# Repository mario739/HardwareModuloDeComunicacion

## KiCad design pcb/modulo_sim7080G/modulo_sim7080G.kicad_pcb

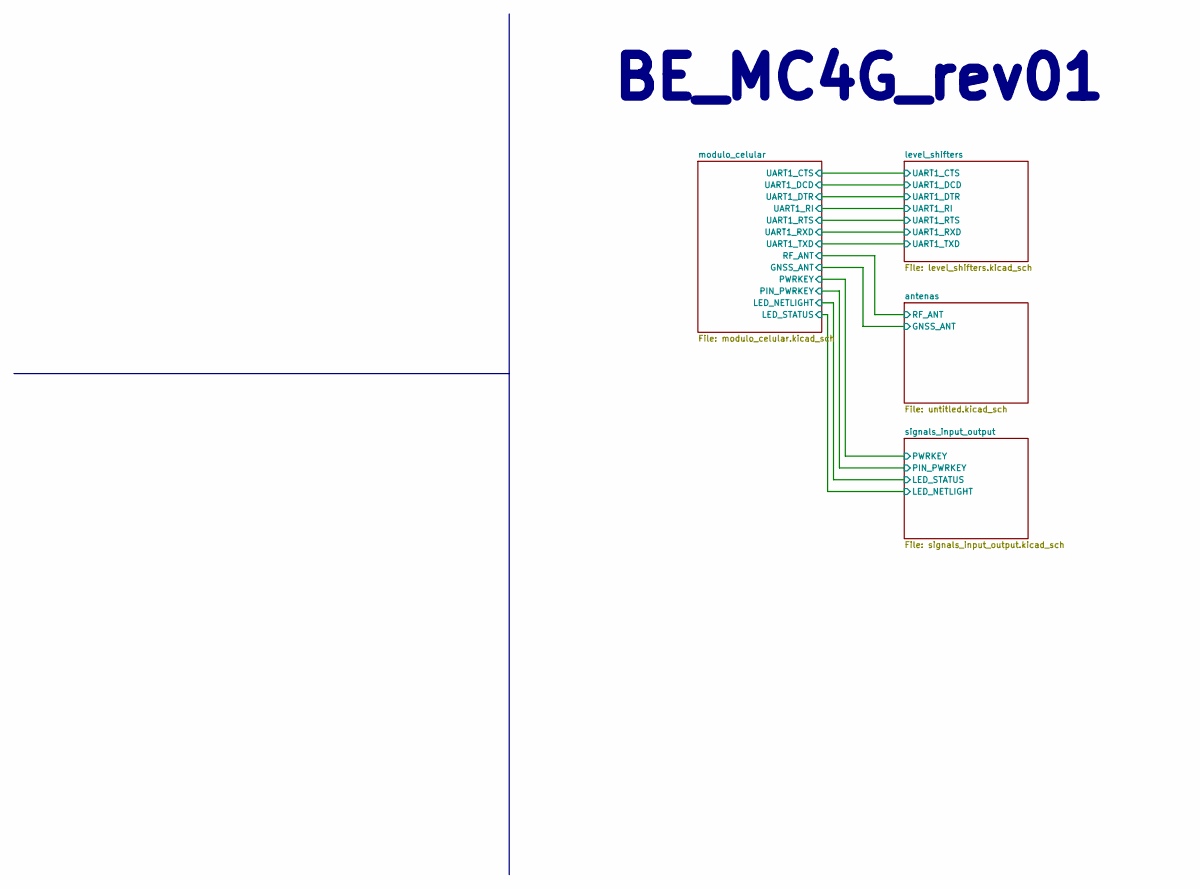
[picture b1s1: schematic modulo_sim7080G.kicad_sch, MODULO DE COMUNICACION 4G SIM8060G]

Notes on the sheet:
BE_MC4G_rev01

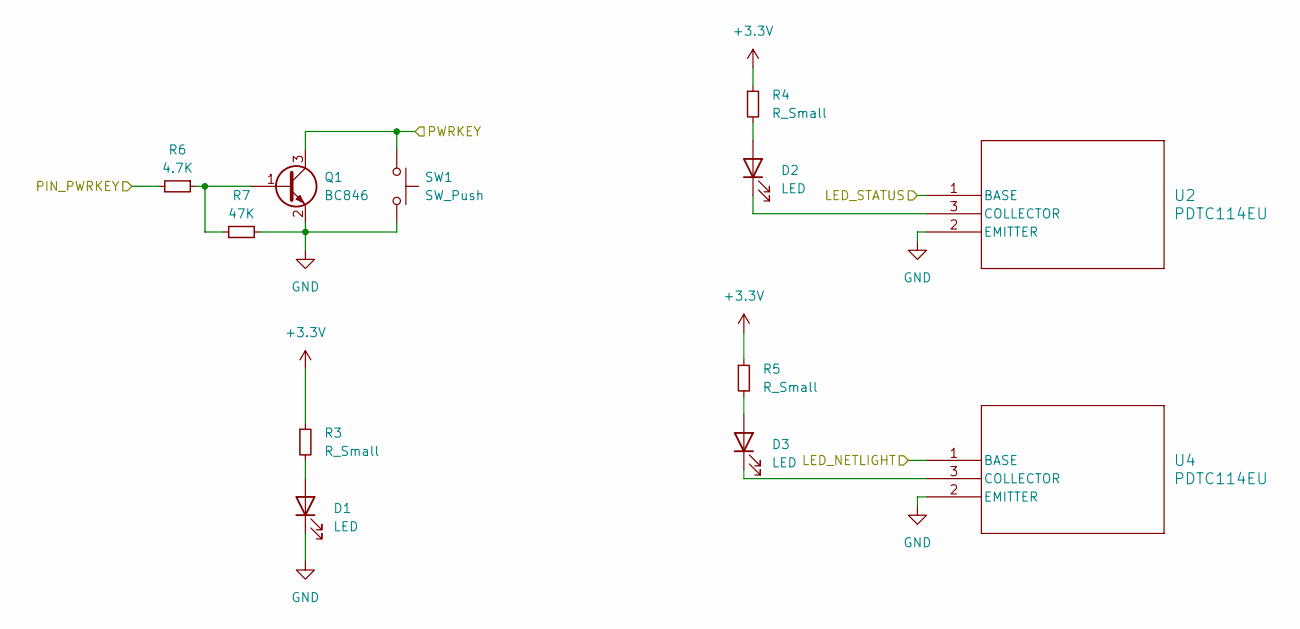
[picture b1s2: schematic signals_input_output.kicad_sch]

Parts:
D1, D2, D3: LED; LED_0805_2012Metric
Q1: BC846; SOT-23
R3, R4, R5: R_Small; R_0402_1005Metric
R6: 4.7K; R_0402_1005Metric
R7: 47K; R_0402_1005Metric
SW1: SW_Push; SW_SPST_B3U-1000P-B
U2, U4: PDTC114EU; SOT323_NEX

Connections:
+3.3V: R3.1, R4.1, R5.1; also elsewhere on the board
/modulo_celular/LED_NETLIGHT: U2.1 (BASE); also elsewhere on the board
/modulo_celular/LED_STATUS: U4.1 (BASE); also elsewhere on the board
/modulo_celular/PIN_PWRKEY: R6.2; also elsewhere on the board
/modulo_celular/PWRKEY: Q1.3 (C), SW1.1; also elsewhere on the board
GND: D1.1 (K), Q1.2 (E), R7.2, SW1.2, U2.2 (EMITTER), U4.2 (EMITTER); also elsewhere on the board
unnamed: D1.2 (A), R3.2
unnamed: D2.2 (A), R4.2
unnamed: D2.1 (K), U2.3 (COLLECTOR)
unnamed: D3.2 (A), R5.2
unnamed: D3.1 (K), U4.3 (COLLECTOR)
unnamed: Q1.1 (B), R6.1, R7.1

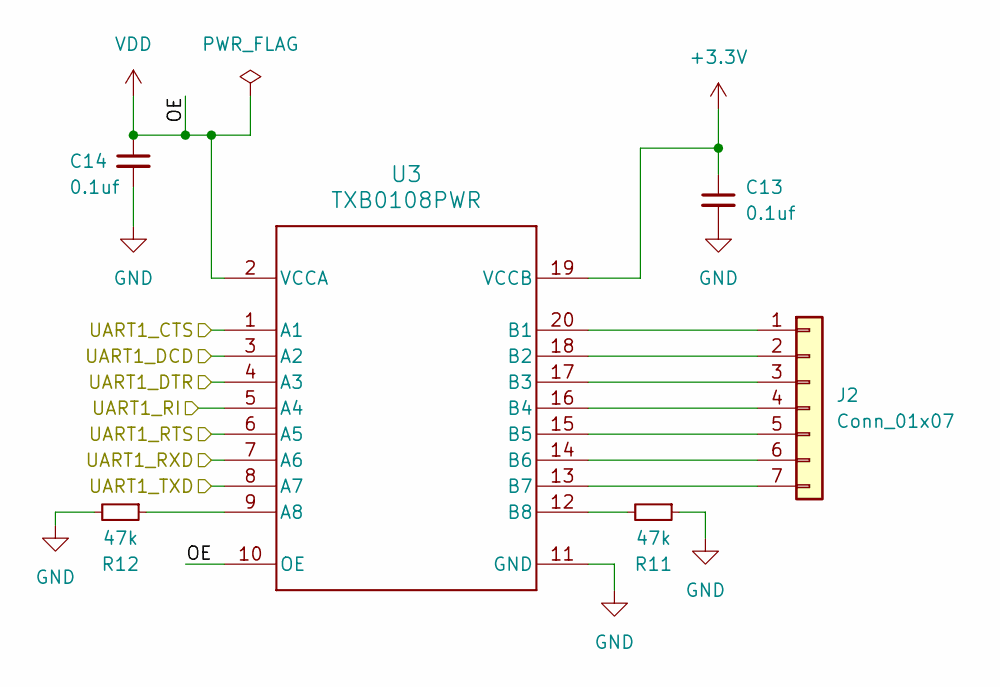
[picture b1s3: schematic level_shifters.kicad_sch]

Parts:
C13, C14: 0.1uf; C_0402_1005Metric
J2: Conn_01x07; PinHeader_1x07_P2.54mm_Vertical
R11, R12: 47k; R_0402_1005Metric
U3: TXB0108PWR; PW0020A_N

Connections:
+3.3V: C13.1, U3.19 (VCCB); also elsewhere on the board
/level_shifters/UART1_CTS: U3.1 (A1); also elsewhere on the board
/level_shifters/UART1_DCD: U3.3 (A2); also elsewhere on the board
/level_shifters/UART1_DTR: U3.4 (A3); also elsewhere on the board
/level_shifters/UART1_RI: U3.5 (A4); also elsewhere on the board
/level_shifters/UART1_RTS: U3.6 (A5); also elsewhere on the board
/level_shifters/UART1_RXD: U3.7 (A6); also elsewhere on the board
/level_shifters/UART1_TXD: U3.8 (A7); also elsewhere on the board
GND: C13.2, C14.2, R11.1, R12.2, U3.11 (GND); also elsewhere on the board
unnamed: J2.1, U3.20 (B1)
unnamed: J2.2, U3.18 (B2)
unnamed: J2.3, U3.17 (B3)
unnamed: J2.4, U3.16 (B4)
unnamed: J2.5, U3.15 (B5)
unnamed: J2.6, U3.14 (B6)
unnamed: J2.7, U3.13 (B7)
unnamed: R12.1, U3.9 (A8)
unnamed: R11.2, U3.12 (B8)
VDD: C14.1, U3.2 (VCCA), U3.10 (OE); also elsewhere on the board

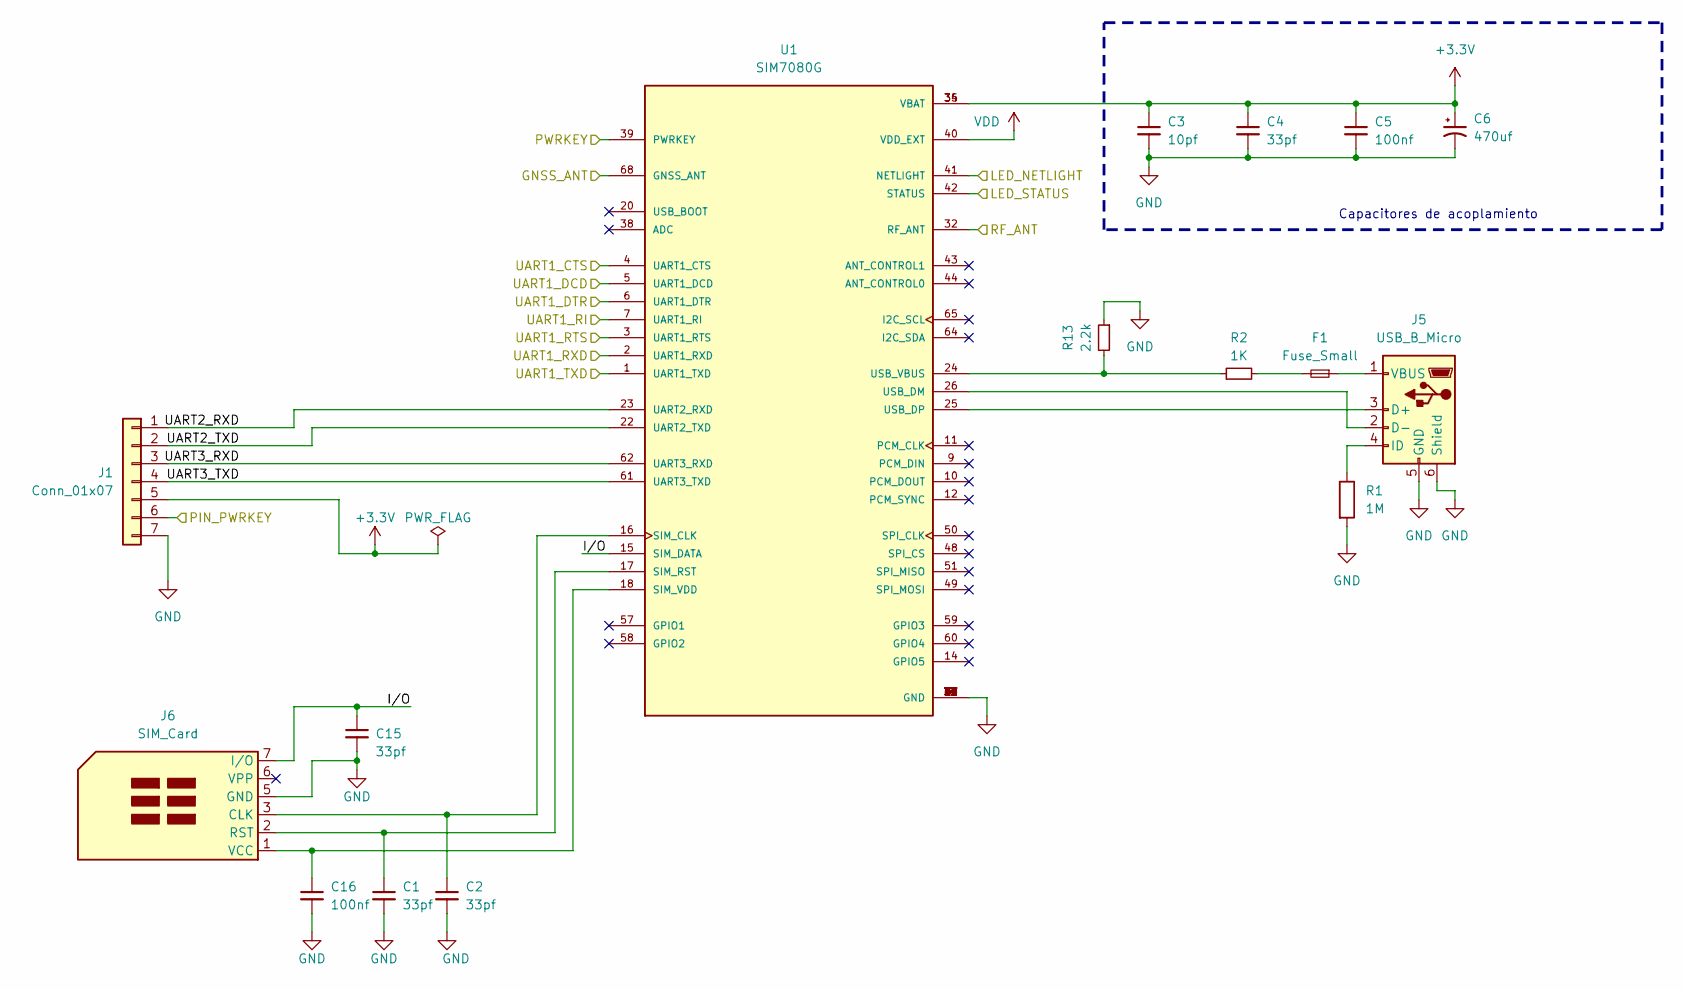
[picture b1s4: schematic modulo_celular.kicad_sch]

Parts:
C1, C2, C4, C15: 33pf; C_0402_1005Metric
C3: 10pf; C_0805_2012Metric
C5, C16: 100nf; C_0402_1005Metric
C6: 470uf; CP_EIA-2012-12_Kemet-R
F1: Fuse_Small; Fuse_0402_1005Metric
J1: Conn_01x07; PinHeader_1x07_P2.54mm_Vertical
J5: USB_B_Micro; USB_Micro-B_Molex_47346-0001
J6: SIM_Card
R1: 1M; R_0402_1005Metric
R2: 1K; R_0402_1005Metric
R13: 2.2k; R_0402_1005Metric
U1: SIM7080G; XCVR_SIM7080G; PARTREV 1.04

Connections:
+3.3V: C3.1, C4.1, C5.1, C6.1, J1.5, U1.34 (VBAT), U1.35 (VBAT); also elsewhere on the board
/antenas/GNSS_ANT: U1.68 (GNSS_ANT)
/antenas/RF_ANT: U1.32 (RF_ANT); also elsewhere on the board
/level_shifters/UART1_CTS: U1.4 (UART1_CTS); also elsewhere on the board
/level_shifters/UART1_DCD: U1.5 (UART1_DCD); also elsewhere on the board
/level_shifters/UART1_DTR: U1.6 (UART1_DTR); also elsewhere on the board
/level_shifters/UART1_RI: U1.7 (UART1_RI); also elsewhere on the board
/level_shifters/UART1_RTS: U1.3 (UART1_RTS); also elsewhere on the board
/level_shifters/UART1_RXD: U1.2 (UART1_RXD); also elsewhere on the board
/level_shifters/UART1_TXD: U1.1 (UART1_TXD); also elsewhere on the board
/modulo_celular/I/O: C15.1, J6.7 (I/O), U1.15 (SIM_DATA)
/modulo_celular/LED_NETLIGHT: U1.41 (NETLIGHT); also elsewhere on the board
/modulo_celular/LED_STATUS: U1.42 (STATUS); also elsewhere on the board
/modulo_celular/PIN_PWRKEY: J1.6; also elsewhere on the board
/modulo_celular/PWRKEY: U1.39 (PWRKEY); also elsewhere on the board
/modulo_celular/UART2_RXD: J1.1, U1.23 (UART2_RXD)
/modulo_celular/UART2_TXD: J1.2, U1.22 (UART2_TXD)
/modulo_celular/UART3_RXD: J1.3, U1.62 (UART3_RXD)
/modulo_celular/UART3_TXD: J1.4, U1.61 (UART3_TXD)
GND: C1.2, C2.2, C3.2, C4.2, C5.2, C6.2, C15.2, C16.2, J1.7, J5.5 (GND), J5.6 (Shield), J6.5 (GND), R1.2, R13.1, U1.8 (GND), U1.13 (GND), U1.19 (GND), U1.21 (GND), U1.27 (GND), U1.30 (GND), U1.31 (GND), U1.33 (GND), U1.36 (GND), U1.37 (GND), U1.45 (GND), U1.63 (GND), U1.66 (GND), U1.67 (GND), U1.69 (GND), U1.70 (GND), U1.71 (GND), U1.72 (GND), U1.73 (GND), U1.74 (GND), U1.75 (GND), U1.76 (GND), U1.77 (GND); also elsewhere on the board
unnamed: F1.2, R2.2
unnamed: J5.3 (D+), U1.25 (USB_DP)
unnamed: J5.2 (D-), U1.26 (USB_DM)
unnamed: J5.4 (ID), R1.1
unnamed: F1.1, J5.1 (VBUS)
unnamed: C2.1, J6.3 (CLK), U1.16 (SIM_CLK)
unnamed: C1.1, J6.2 (RST), U1.17 (SIM_RST)
unnamed: C16.1, J6.1 (VCC), U1.18 (SIM_VDD)
unnamed: R2.1, R13.2, U1.24 (USB_VBUS)
VDD: U1.40 (VDD_EXT); also elsewhere on the board

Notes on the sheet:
Capacitores de acoplamiento

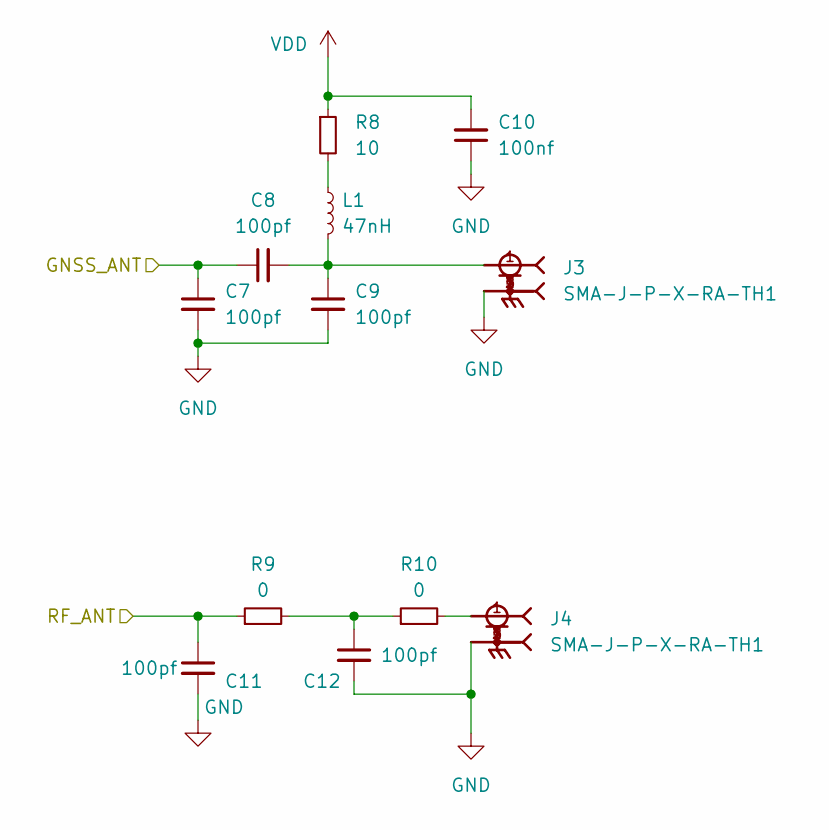
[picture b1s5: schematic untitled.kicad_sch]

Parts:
C7, C8, C9, C11, C12: 100pf; C_0402_1005Metric
C10: 100nf; C_0402_1005Metric
J3, J4: SMA-J-P-X-RA-TH1; SAMTEC_SMA-J-P-X-RA-TH1; PARTREV K
L1: 47nH; L_0805_2012Metric
R8: 10; R_0402_1005Metric
R9, R10: 0; R_0402_1005Metric

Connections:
/GNSS_ANT: C7.1, C8.1
/antenas/RF_ANT: C11.1, R9.1; also elsewhere on the board
GND: C7.2, C9.2, C10.1, C11.2, C12.2, J3.2, J3.3, J3.4, J3.5, J4.2, J4.3, J4.4, J4.5; also elsewhere on the board
unnamed: C8.2, C9.1, J3.1, L1.2
unnamed: C12.1, R9.2, R10.1
unnamed: J4.1, R10.2
unnamed: L1.1, R8.2
VDD: C10.2, R8.1; also elsewhere on the board

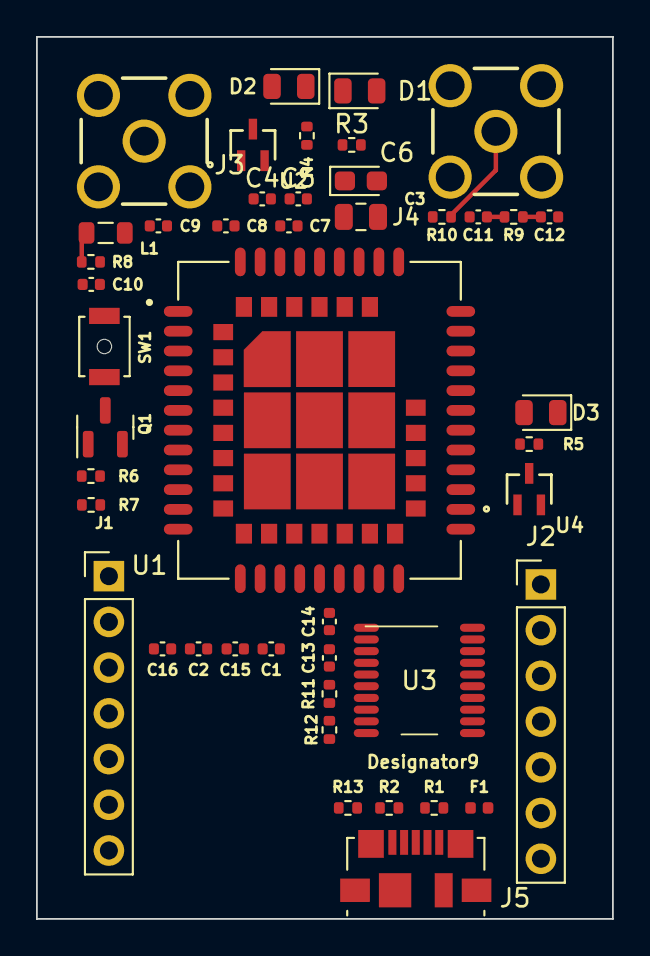
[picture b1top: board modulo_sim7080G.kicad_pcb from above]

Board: 2 copper layers, 32.0 x 49.0 mm, 45 parts (0 on the bottom side), 49 nets.

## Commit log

2023-08-10 first commit,schematic and pcb included
2023-08-12 update schematic
2023-12-26 antes del gitignore
2023-12-26 se adiciono el archivo .gitignore
2023-12-26 antes del CADLAB
2023-12-28 se ordenaron los componentes en el pcb
